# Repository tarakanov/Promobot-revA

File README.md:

Promobot
=============

Main board for Promobot, robotic platform. Still in development.

Schematic and layout done in Eagle.
Board has four VNH5019A-E H-bridge drivers for high current DC brushed motors, 50W 2ch audio amplifier (TPA116D2), two DC/DC step-up converters (TPS43061, up to 40V, 20A), one DC/DC step-down converter (TPS563200, 5V, 3A) and MCU for control (atmega32u4, Arduino Leonardo compatible).

It is initial design, so the board is big and bulky (15x15 cm). The board is manufactured and tested, but the current and power limits was not reached. There is a lot things to cut. Feel free to ask questions and make improvements.

Designed by Semyon Tarakanov. Creative Commons Attribution, Share-Alike license.

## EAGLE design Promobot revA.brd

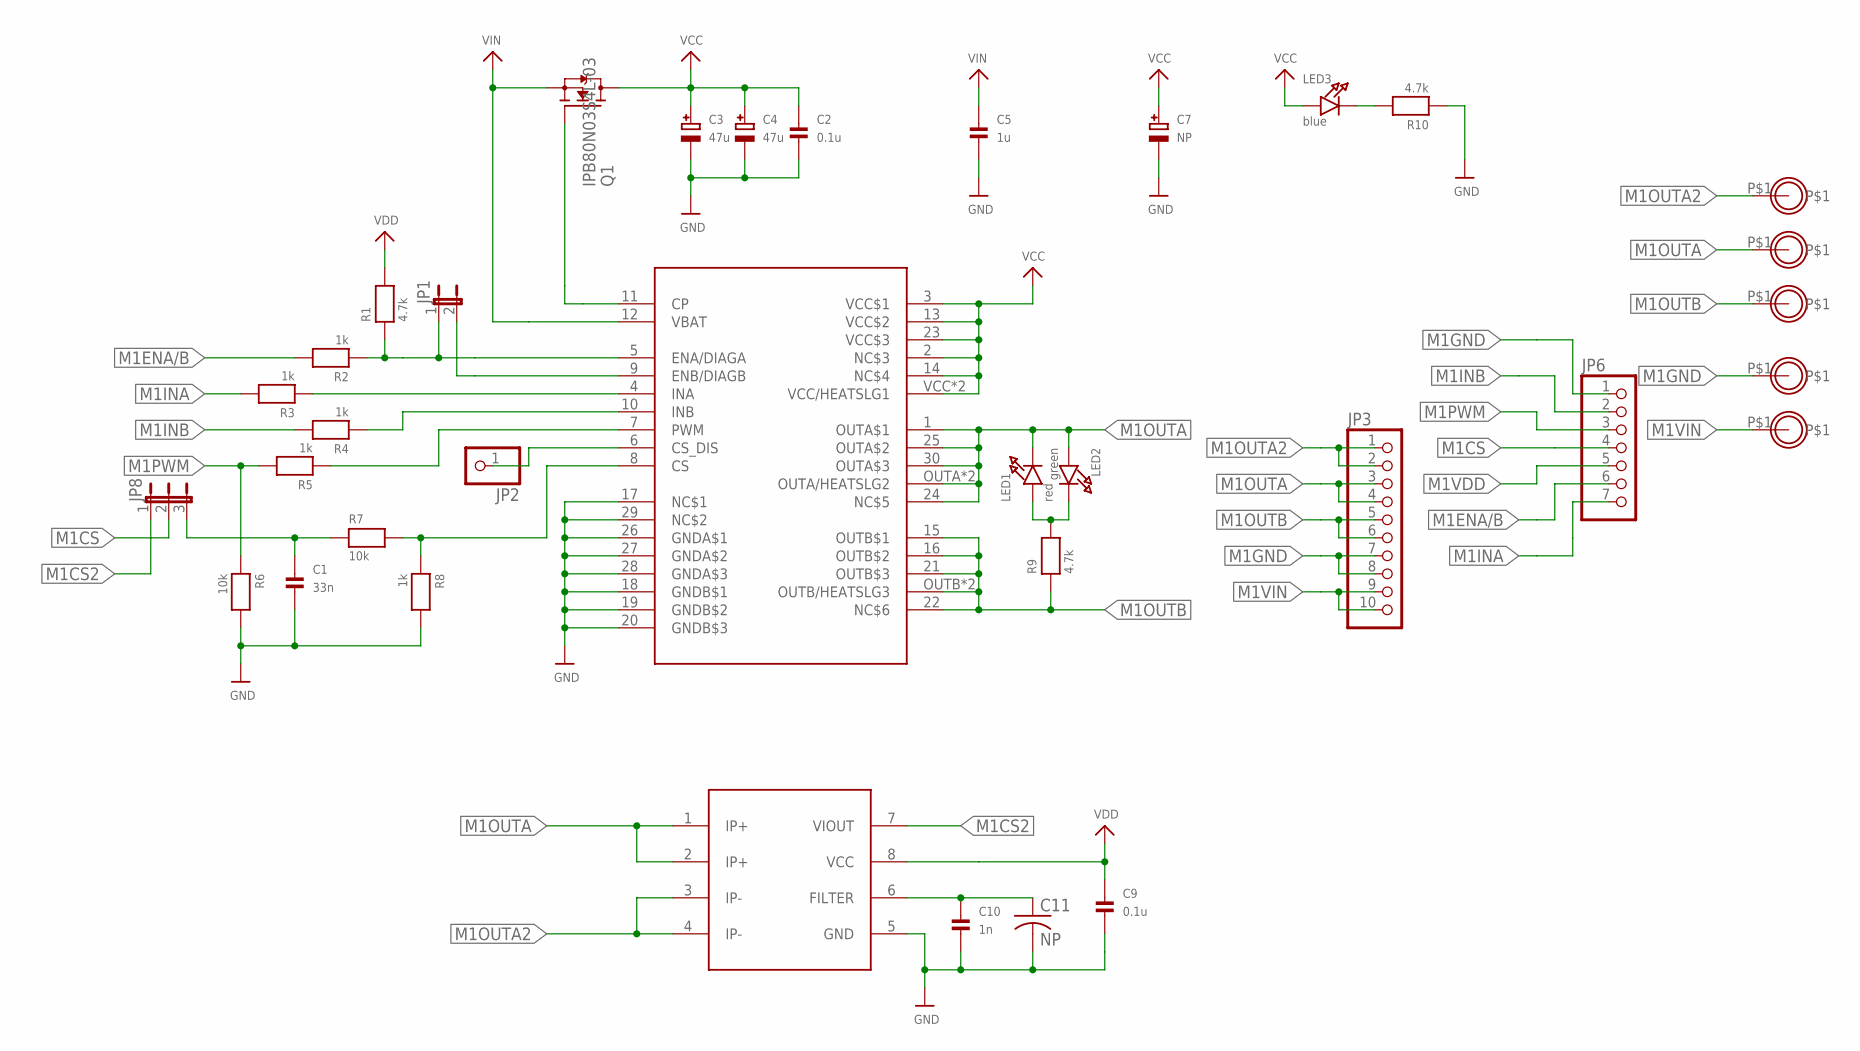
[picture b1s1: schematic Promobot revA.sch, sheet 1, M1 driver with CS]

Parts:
C1: 33n; _0603
C2, C9: 0.1u; _0603
C3, C4: 47u; PANASONIC_C
C5: 1u; _0805
C7: NP; CELEC_3.5MM_10MM
C10: 1n; _0603
C11: NP; C025-024X044
JP1: JUMPER2
JP2: HEADER-1X1ROUND; 1X01_ROUND
JP3: HEADER-1X10ROUND; 1X10_ROUND
JP6: HEADER-1X7ROUND; 1X07_ROUND
JP8: JUMPER3
LED1: red; CHIPLED_0603
LED2: green; CHIPLED_0603
LED3: blue; CHIPLED_0603
M1OUTA, M1OUTA1, M1OUTA3, M1OUTA4, M1OUTB: MOUNTINGHOLE2.5_THICK; MOUNTINGHOLE_2.5_PLATED_THICK
Q1: IPB80N03S4L-03; TO263
R1, R9, R10: 4.7k; 0603
R2, R3, R4, R5, R8: 1k; 0603
R6, R7: 10k; 0603
U1: VNH5019A-E; MULTIPOWERSO-30
U2: ACS714; SOIC8_208MIL

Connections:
M1CS: JP6.4, JP8.2
M1CS1: C1.1, JP8.3, R7.1
M1CS2: JP8.1, U2.7 (VIOUT)
M1ENA/B: JP6.6, R2.2
M1GND: C1.2, C2.2, C3.-, C4.-, C5.2, C7.-, C9.2, C10.2, C11.2, JP3.7, JP3.8, JP6.1, M1OUTA3.P$1, R6.2, R8.2, R10.1, U1.17 (NC$1), U1.18 (GNDB$1), U1.19 (GNDB$2), U1.20 (GNDB$3), U1.26 (GNDA$1), U1.27 (GNDA$2), U1.28 (GNDA$3), U1.29 (NC$2), U2.5 (GND); also elsewhere on the board
M1INA: JP6.7, R3.2
M1INB: JP6.2, R4.2
M1OUTA: JP3.3, JP3.4, LED1.C, LED2.A, M1OUTA1.P$1, U1.1 (OUTA$1), U1.24 (NC$5), U1.25 (OUTA$2), U1.30 (OUTA$3), U1.OUTA (OUTA/HEATSLG2), U1.OUTA@1 (OUTA/HEATSLG2), U2.1 (IP+), U2.2 (IP+)
M1OUTA2: JP3.1, JP3.2, M1OUTA.P$1, U2.3 (IP-), U2.4 (IP-)
M1OUTB: JP3.5, JP3.6, M1OUTB.P$1, R9.1, U1.15 (OUTB$1), U1.16 (OUTB$2), U1.21 (OUTB$3), U1.22 (NC$6), U1.OUTB (OUTB/HEATSLG3), U1.OUTB@1 (OUTB/HEATSLG3)
M1PWM: JP6.3, R5.2, R6.1
M1VCC: C2.1, C3.+, C4.+, C7.+, LED3.A, Q1.3 (D), U1.2 (NC$3), U1.3 (VCC$1), U1.13 (VCC$2), U1.14 (NC$4), U1.23 (VCC$3), U1.VCC (VCC/HEATSLG1), U1.VCC@1 (VCC/HEATSLG1); also elsewhere on the board
M1VDD: C9.1, JP6.5, R1.2, U2.8 (VCC)
M1VIN: C5.1, JP3.9, JP3.10, M1OUTA4.P$1, Q1.2 (S), U1.12 (VBAT)
unnamed: Q1.1 (G), U1.11 (CP)
unnamed: JP1.2, U1.9 (ENB/DIAGB)
unnamed: R5.1, U1.7 (PWM)
unnamed: JP1.1, R1.1, R2.1, U1.5 (ENA/DIAGA)
unnamed: R7.2, R8.1, U1.8 (CS)
unnamed: R3.1, U1.4 (INA)
unnamed: R4.1, U1.10 (INB)
unnamed: JP2.1, U1.6 (CS_DIS)
unnamed: LED3.C, R10.2
unnamed: C10.1, C11.1, U2.6 (FILTER)
unnamed: LED1.A, LED2.C, R9.2

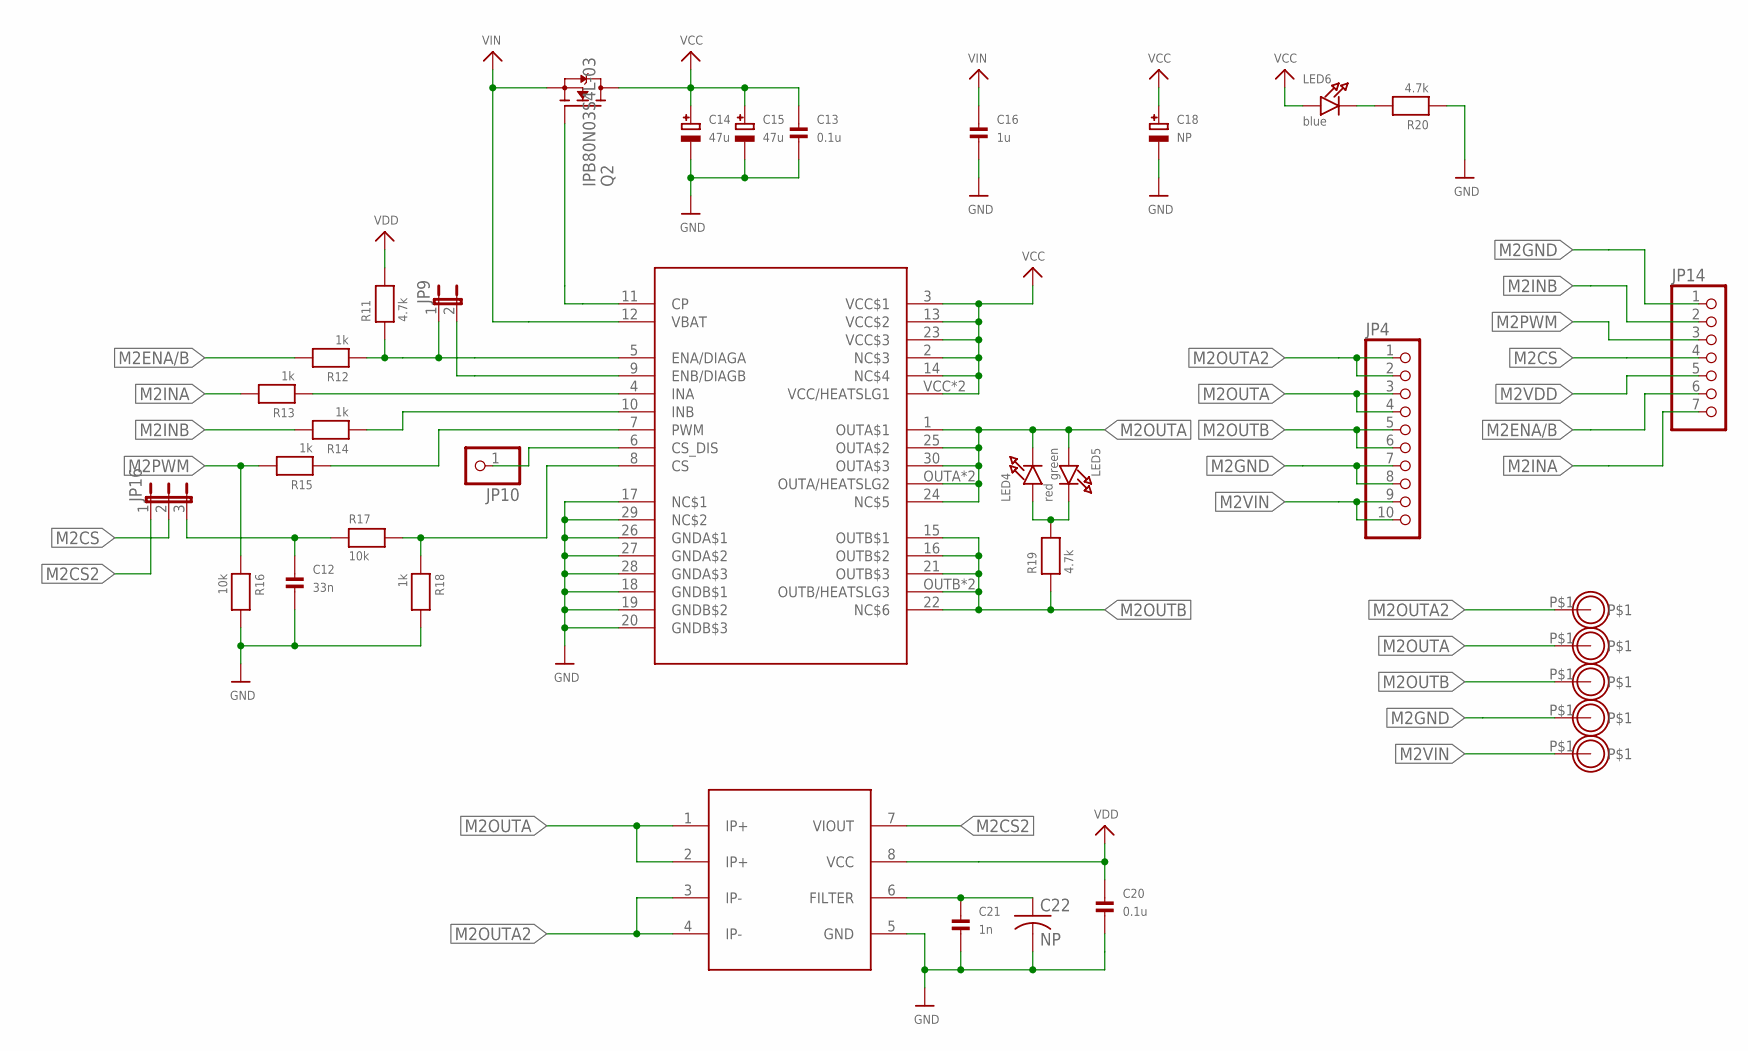
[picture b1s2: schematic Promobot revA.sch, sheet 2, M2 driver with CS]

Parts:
C12: 33n; _0603
C13, C20: 0.1u; _0603
C14, C15: 47u; PANASONIC_C
C16: 1u; _0805
C18: NP; CELEC_3.5MM_10MM
C21: 1n; _0603
C22: NP; C025-024X044
JP4: HEADER-1X10ROUND; 1X10_ROUND
JP9: JUMPER2
JP10: HEADER-1X1ROUND; 1X01_ROUND
JP14: HEADER-1X7ROUND; 1X07_ROUND
JP16: JUMPER3
LED4: red; CHIPLED_0603
LED5: green; CHIPLED_0603
LED6: blue; CHIPLED_0603
M1OUTA2, M1OUTA5, M1OUTA6, M1OUTA7, M1OUTB1: MOUNTINGHOLE2.5_THICK; MOUNTINGHOLE_2.5_PLATED_THICK
Q2: IPB80N03S4L-03; TO263
R11, R19, R20: 4.7k; 0603
R12, R13, R14, R15, R18: 1k; 0603
R16, R17: 10k; 0603
U3: VNH5019A-E; MULTIPOWERSO-30
U4: ACS714; SOIC8_208MIL

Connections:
M2CS: JP14.4, JP16.2
M2CS2: JP16.1, U4.7 (VIOUT)
M2ENA/B: JP14.6, R12.2
M2GND: C12.2, C13.2, C14.-, C15.-, C16.2, C18.-, C20.2, C21.2, C22.2, JP4.7, JP4.8, JP14.1, M1OUTA6.P$1, R16.2, R18.2, R20.1, U3.17 (NC$1), U3.18 (GNDB$1), U3.19 (GNDB$2), U3.20 (GNDB$3), U3.26 (GNDA$1), U3.27 (GNDA$2), U3.28 (GNDA$3), U3.29 (NC$2), U4.5 (GND); also elsewhere on the board
M2INA: JP14.7, R13.2
M2INB: JP14.2, R14.2
M2OUTA: JP4.3, JP4.4, LED4.C, LED5.A, M1OUTA5.P$1, U3.1 (OUTA$1), U3.24 (NC$5), U3.25 (OUTA$2), U3.30 (OUTA$3), U3.OUTA (OUTA/HEATSLG2), U3.OUTA@1 (OUTA/HEATSLG2), U4.1 (IP+), U4.2 (IP+)
M2OUTA2: JP4.1, JP4.2, M1OUTA2.P$1, U4.3 (IP-), U4.4 (IP-)
M2OUTB: JP4.5, JP4.6, M1OUTB1.P$1, R19.1, U3.15 (OUTB$1), U3.16 (OUTB$2), U3.21 (OUTB$3), U3.22 (NC$6), U3.OUTB (OUTB/HEATSLG3), U3.OUTB@1 (OUTB/HEATSLG3)
M2PWM: JP14.3, R15.2, R16.1
M2VCC: C13.1, C14.+, C15.+, C18.+, LED6.A, Q2.3 (D), U3.2 (NC$3), U3.3 (VCC$1), U3.13 (VCC$2), U3.14 (NC$4), U3.23 (VCC$3), U3.VCC (VCC/HEATSLG1), U3.VCC@1 (VCC/HEATSLG1); also elsewhere on the board
M2VDD: C20.1, JP14.5, R11.2, U4.8 (VCC)
M2VIN: C16.1, JP4.9, JP4.10, M1OUTA7.P$1, Q2.2 (S), U3.12 (VBAT)
unnamed: Q2.1 (G), U3.11 (CP)
unnamed: JP9.1, R11.1, R12.1, U3.5 (ENA/DIAGA)
unnamed: JP9.2, U3.9 (ENB/DIAGB)
unnamed: R13.1, U3.4 (INA)
unnamed: R14.1, U3.10 (INB)
unnamed: R15.1, U3.7 (PWM)
unnamed: R17.2, R18.1, U3.8 (CS)
unnamed: JP10.1, U3.6 (CS_DIS)
unnamed: LED4.A, LED5.C, R19.2
unnamed: LED6.C, R20.2
unnamed: C21.1, C22.1, U4.6 (FILTER)
unnamed: C12.1, JP16.3, R17.1

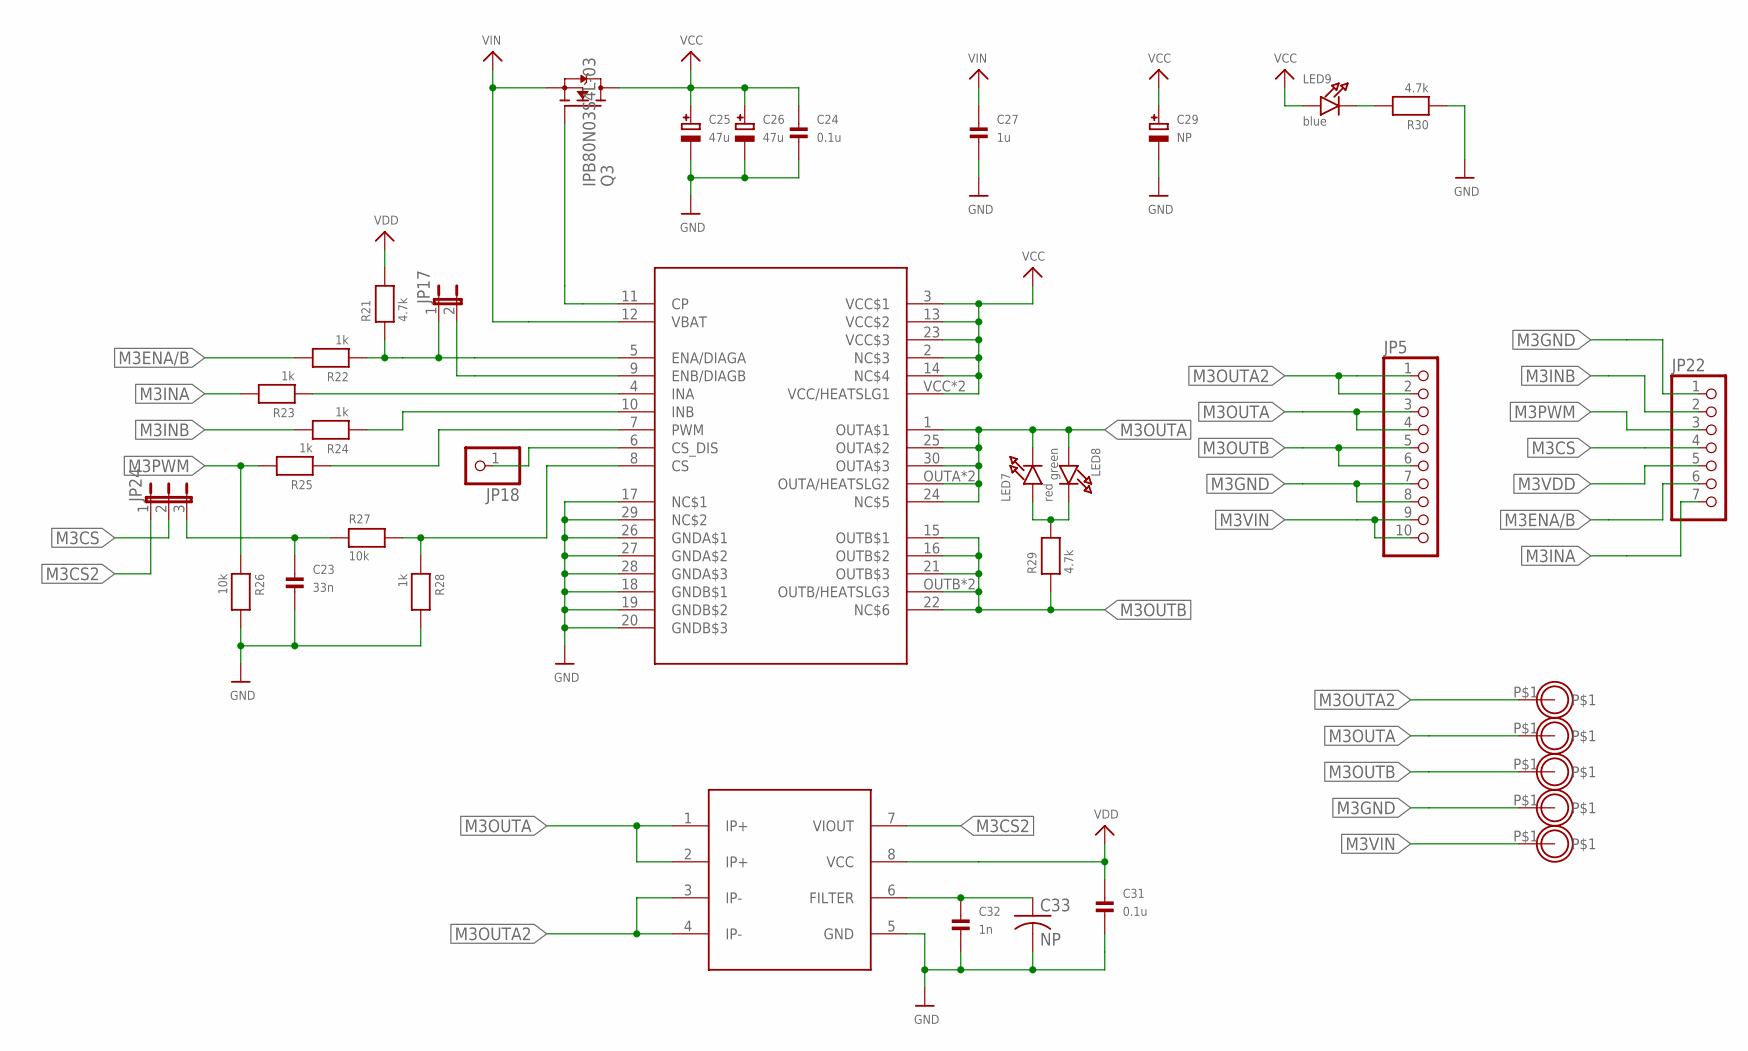
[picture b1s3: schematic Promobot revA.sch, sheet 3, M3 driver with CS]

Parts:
C23: 33n; _0603
C24, C31: 0.1u; _0603
C25, C26: 47u; PANASONIC_C
C27: 1u; _0805
C29: NP; CELEC_3.5MM_10MM
C32: 1n; _0603
C33: NP; C025-024X044
JP5: HEADER-1X10ROUND; 1X10_ROUND
JP17: JUMPER2
JP18: HEADER-1X1ROUND; 1X01_ROUND
JP22: HEADER-1X7ROUND; 1X07_ROUND
JP24: JUMPER3
LED7: red; CHIPLED_0603
LED8: green; CHIPLED_0603
LED9: blue; CHIPLED_0603
M1OUTA8, M1OUTA9, M1OUTA10, M1OUTA11, M1OUTB2: MOUNTINGHOLE2.5_THICK; MOUNTINGHOLE_2.5_PLATED_THICK
Q3: IPB80N03S4L-03; TO263
R21, R29, R30: 4.7k; 0603
R22, R23, R24, R25, R28: 1k; 0603
R26, R27: 10k; 0603
U5: VNH5019A-E; MULTIPOWERSO-30
U6: ACS714; SOIC8_208MIL

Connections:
M3CS: JP22.4, JP24.2
M3CS2: JP24.1, U6.7 (VIOUT)
M3ENA/B: JP22.6, R22.2
M3GND: C23.2, C24.2, C25.-, C26.-, C27.2, C29.-, C31.2, C32.2, C33.2, JP5.7, JP5.8, JP22.1, M1OUTA10.P$1, R26.2, R28.2, R30.1, U5.17 (NC$1), U5.18 (GNDB$1), U5.19 (GNDB$2), U5.20 (GNDB$3), U5.26 (GNDA$1), U5.27 (GNDA$2), U5.28 (GNDA$3), U5.29 (NC$2), U6.5 (GND); also elsewhere on the board
M3INA: JP22.7, R23.2
M3INB: JP22.2, R24.2
M3OUTA: JP5.3, JP5.4, LED7.C, LED8.A, M1OUTA9.P$1, U5.1 (OUTA$1), U5.24 (NC$5), U5.25 (OUTA$2), U5.30 (OUTA$3), U5.OUTA (OUTA/HEATSLG2), U5.OUTA@1 (OUTA/HEATSLG2), U6.1 (IP+), U6.2 (IP+)
M3OUTA2: JP5.1, JP5.2, M1OUTA8.P$1, U6.3 (IP-), U6.4 (IP-)
M3OUTB: JP5.5, JP5.6, M1OUTB2.P$1, R29.1, U5.15 (OUTB$1), U5.16 (OUTB$2), U5.21 (OUTB$3), U5.22 (NC$6), U5.OUTB (OUTB/HEATSLG3), U5.OUTB@1 (OUTB/HEATSLG3)
M3PWM: JP22.3, R25.2, R26.1
M3VCC: C24.1, C25.+, C26.+, C29.+, LED9.A, Q3.3 (D), U5.2 (NC$3), U5.3 (VCC$1), U5.13 (VCC$2), U5.14 (NC$4), U5.23 (VCC$3), U5.VCC (VCC/HEATSLG1), U5.VCC@1 (VCC/HEATSLG1); also elsewhere on the board
M3VDD: C31.1, JP22.5, R21.2, U6.8 (VCC)
M3VIN: C27.1, JP5.9, JP5.10, M1OUTA11.P$1, Q3.2 (S), U5.12 (VBAT)
unnamed: Q3.1 (G), U5.11 (CP)
unnamed: JP17.1, R21.1, R22.1, U5.5 (ENA/DIAGA)
unnamed: JP17.2, U5.9 (ENB/DIAGB)
unnamed: R23.1, U5.4 (INA)
unnamed: R24.1, U5.10 (INB)
unnamed: R25.1, U5.7 (PWM)
unnamed: R27.2, R28.1, U5.8 (CS)
unnamed: JP18.1, U5.6 (CS_DIS)
unnamed: LED7.A, LED8.C, R29.2
unnamed: LED9.C, R30.2
unnamed: C32.1, C33.1, U6.6 (FILTER)
unnamed: C23.1, JP24.3, R27.1

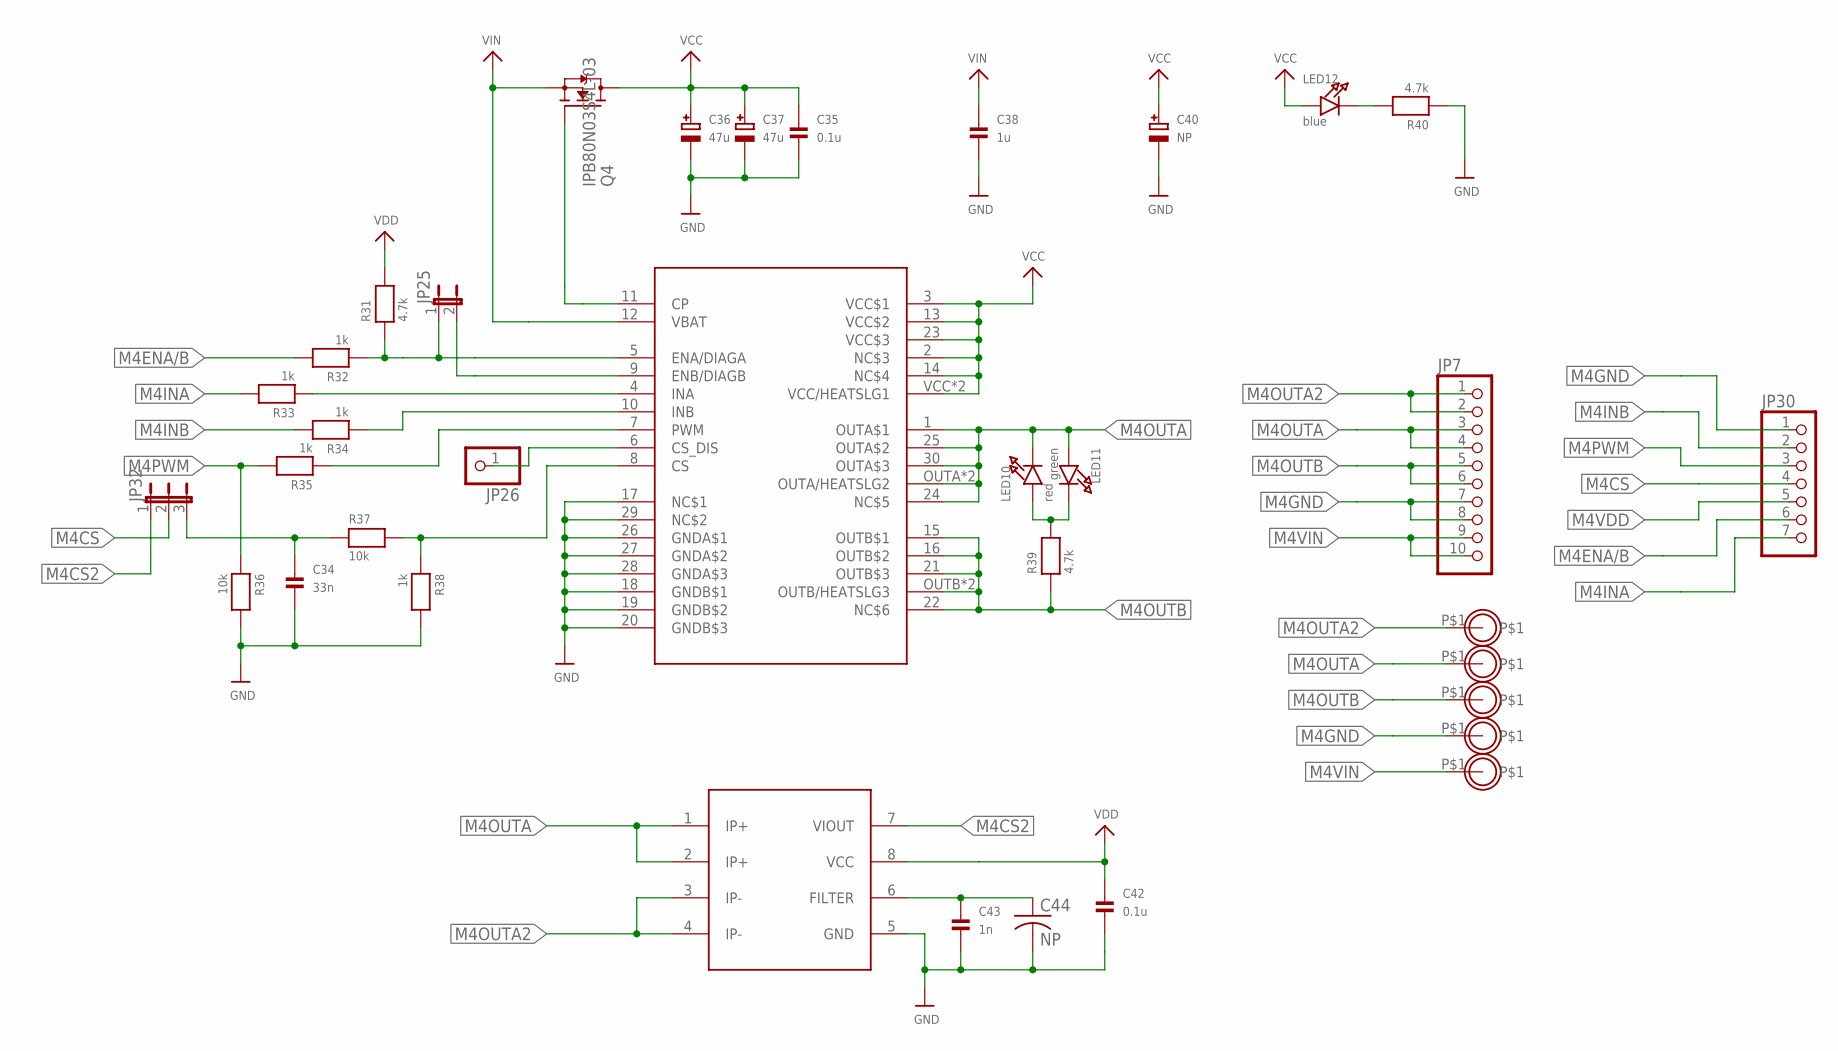
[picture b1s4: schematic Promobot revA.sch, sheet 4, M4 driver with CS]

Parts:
C34: 33n; _0603
C35, C42: 0.1u; _0603
C36, C37: 47u; PANASONIC_C
C38: 1u; _0805
C40: NP; CELEC_3.5MM_10MM
C43: 1n; _0603
C44: NP; C025-024X044
JP7: HEADER-1X10ROUND; 1X10_ROUND
JP25: JUMPER2
JP26: HEADER-1X1ROUND; 1X01_ROUND
JP30: HEADER-1X7ROUND; 1X07_ROUND
JP32: JUMPER3
LED10: red; CHIPLED_0603
LED11: green; CHIPLED_0603
LED12: blue; CHIPLED_0603
M1OUTA12, M1OUTA13, M1OUTA14, M1OUTA15, M1OUTB3: MOUNTINGHOLE2.5_THICK; MOUNTINGHOLE_2.5_PLATED_THICK
Q4: IPB80N03S4L-03; TO263
R31, R39, R40: 4.7k; 0603
R32, R33, R34, R35, R38: 1k; 0603
R36, R37: 10k; 0603
U7: VNH5019A-E; MULTIPOWERSO-30
U8: ACS714; SOIC8_208MIL

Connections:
M4CS: JP30.4, JP32.2
M4CS2: JP32.1, U8.7 (VIOUT)
M4ENA/B: JP30.6, R32.2
M4GND: C34.2, C35.2, C36.-, C37.-, C38.2, C40.-, C42.2, C43.2, C44.2, JP7.7, JP7.8, JP30.1, M1OUTA14.P$1, R36.2, R38.2, R40.1, U7.17 (NC$1), U7.18 (GNDB$1), U7.19 (GNDB$2), U7.20 (GNDB$3), U7.26 (GNDA$1), U7.27 (GNDA$2), U7.28 (GNDA$3), U7.29 (NC$2), U8.5 (GND); also elsewhere on the board
M4INA: JP30.7, R33.2
M4INB: JP30.2, R34.2
M4OUTA: JP7.3, JP7.4, LED10.C, LED11.A, M1OUTA13.P$1, U7.1 (OUTA$1), U7.24 (NC$5), U7.25 (OUTA$2), U7.30 (OUTA$3), U7.OUTA (OUTA/HEATSLG2), U7.OUTA@1 (OUTA/HEATSLG2), U8.1 (IP+), U8.2 (IP+)
M4OUTA2: JP7.1, JP7.2, M1OUTA12.P$1, U8.3 (IP-), U8.4 (IP-)
M4OUTB: JP7.5, JP7.6, M1OUTB3.P$1, R39.1, U7.15 (OUTB$1), U7.16 (OUTB$2), U7.21 (OUTB$3), U7.22 (NC$6), U7.OUTB (OUTB/HEATSLG3), U7.OUTB@1 (OUTB/HEATSLG3)
M4PWM: JP30.3, R35.2, R36.1
M4VCC: C35.1, C36.+, C37.+, C40.+, LED12.A, Q4.3 (D), U7.2 (NC$3), U7.3 (VCC$1), U7.13 (VCC$2), U7.14 (NC$4), U7.23 (VCC$3), U7.VCC (VCC/HEATSLG1), U7.VCC@1 (VCC/HEATSLG1); also elsewhere on the board
M4VDD: C42.1, JP30.5, R31.2, U8.8 (VCC)
M4VIN: C38.1, JP7.9, JP7.10, M1OUTA15.P$1, Q4.2 (S), U7.12 (VBAT)
unnamed: Q4.1 (G), U7.11 (CP)
unnamed: JP25.1, R31.1, R32.1, U7.5 (ENA/DIAGA)
unnamed: JP25.2, U7.9 (ENB/DIAGB)
unnamed: R33.1, U7.4 (INA)
unnamed: R34.1, U7.10 (INB)
unnamed: R35.1, U7.7 (PWM)
unnamed: R37.2, R38.1, U7.8 (CS)
unnamed: JP26.1, U7.6 (CS_DIS)
unnamed: LED10.A, LED11.C, R39.2
unnamed: LED12.C, R40.2
unnamed: C43.1, C44.1, U8.6 (FILTER)
unnamed: C34.1, JP32.3, R37.1

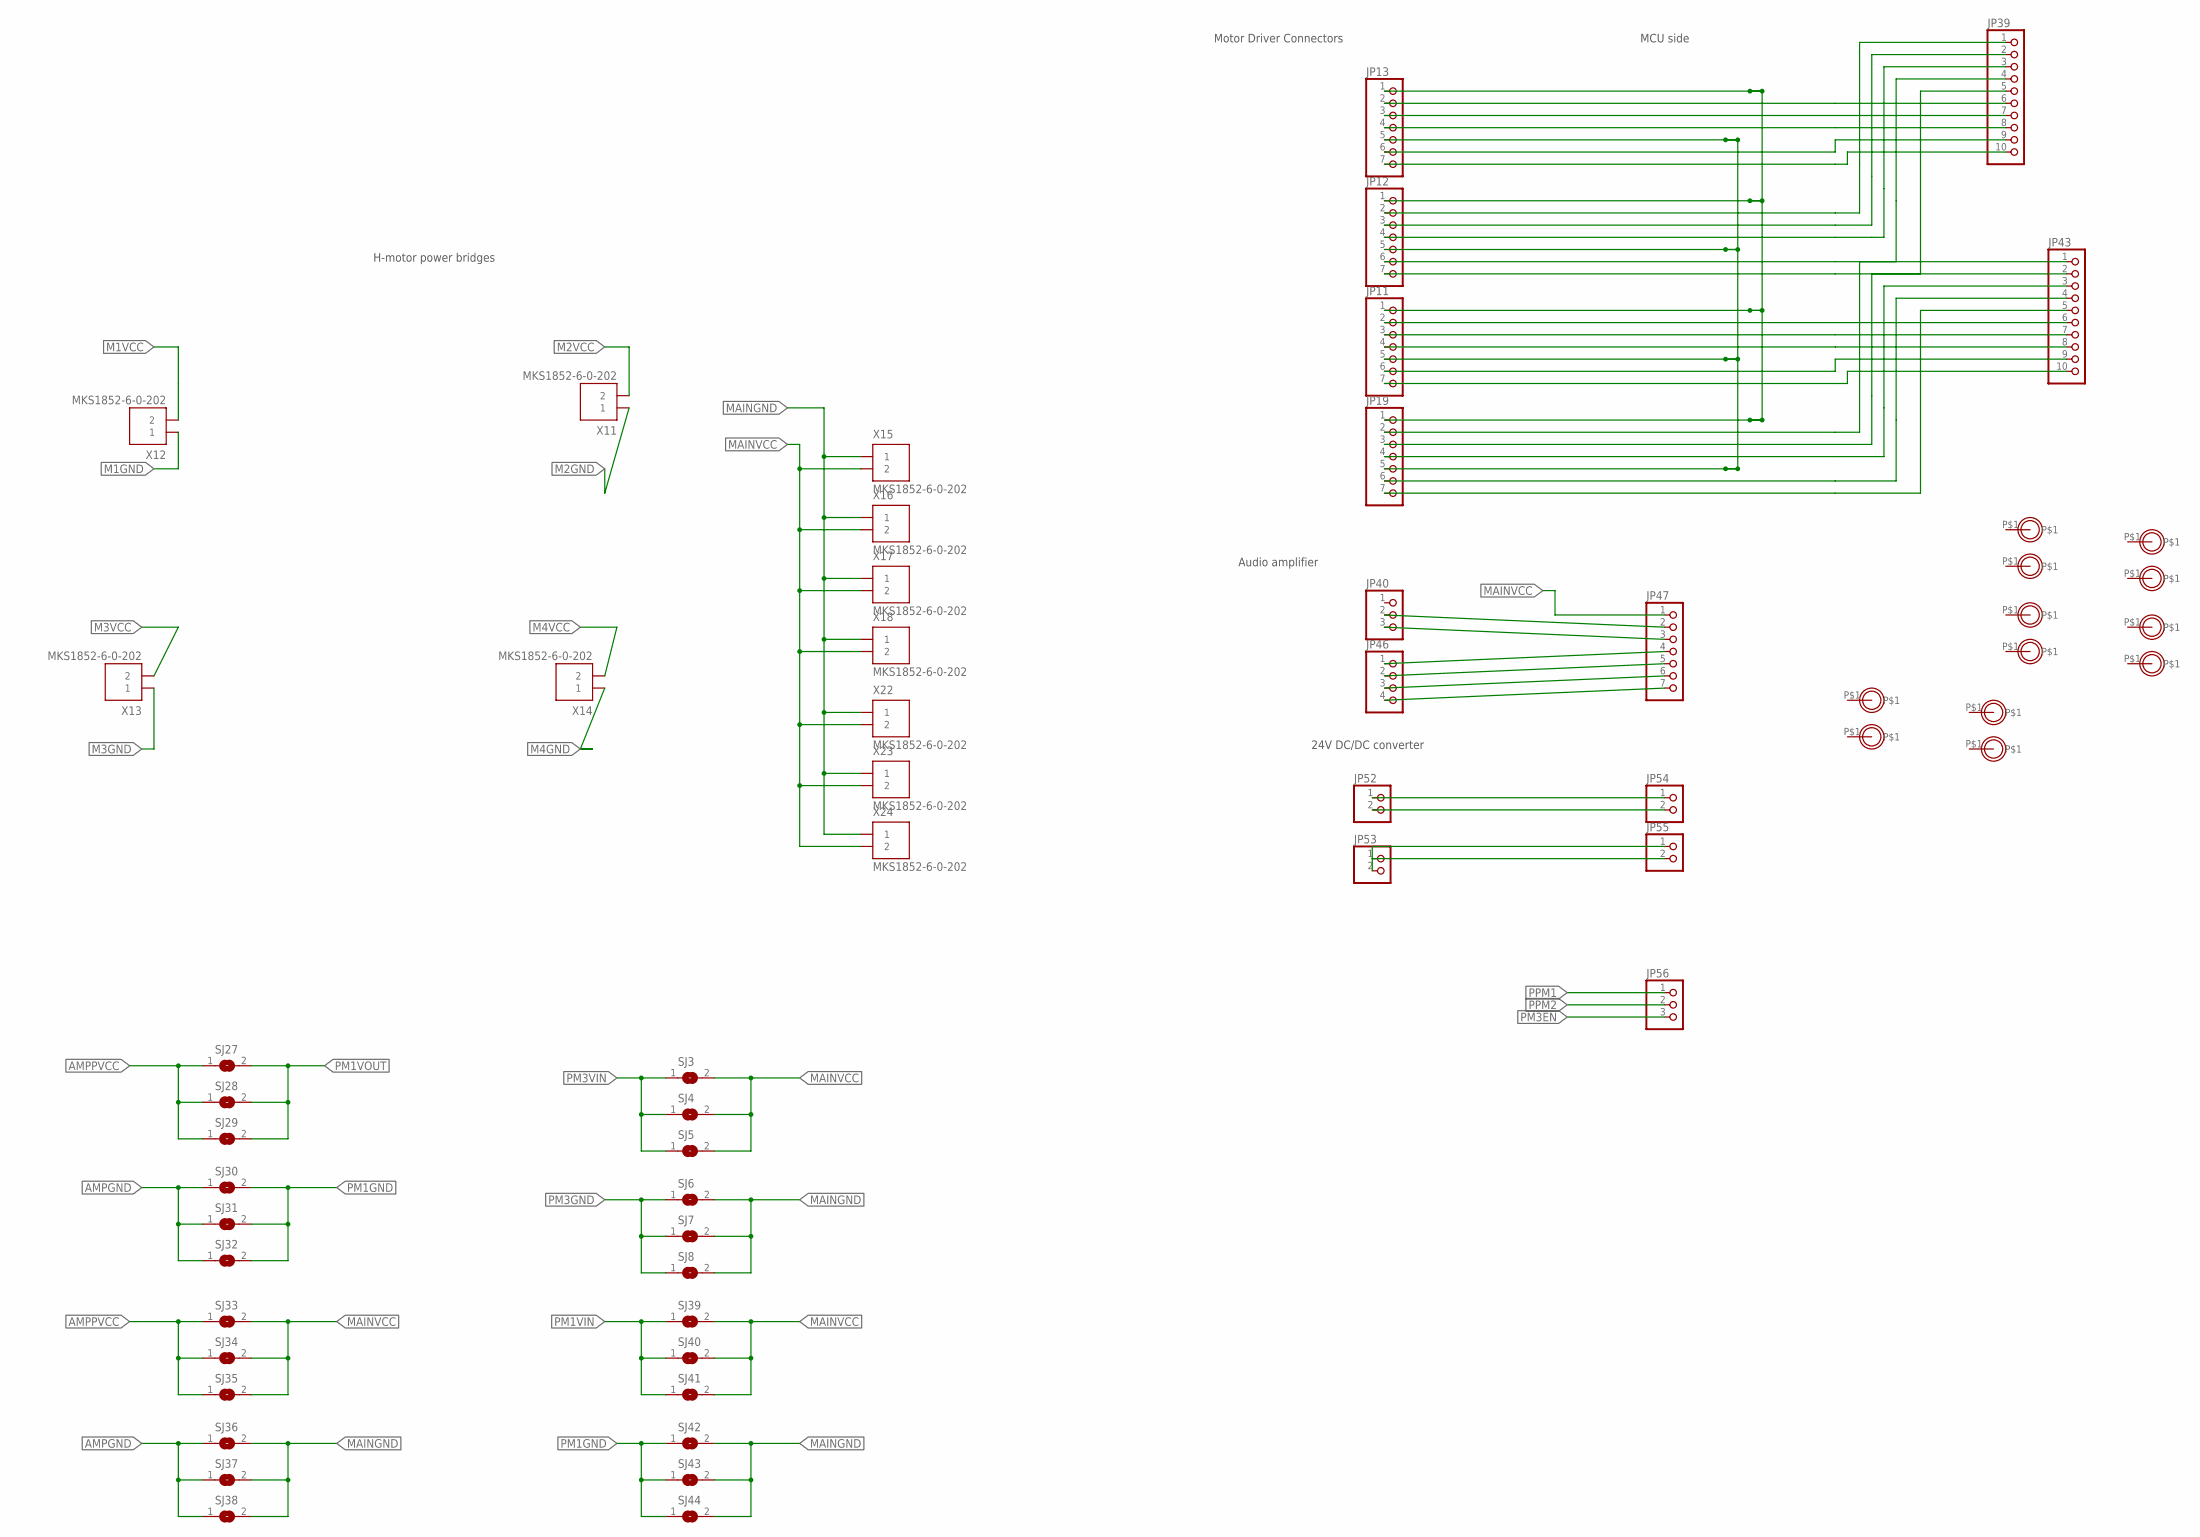
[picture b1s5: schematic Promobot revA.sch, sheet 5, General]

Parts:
JP11, JP12, JP13, JP19, JP47: HEADER-1X7ROUND; 1X07_ROUND
JP39, JP43: HEADER-1X1070MIL; 1X10_ROUND70
JP40: HEADER-1X376MIL; 1X03_ROUND_76
JP46: HEADER-1X476MIL; 1X04_ROUND_76
JP52, JP53, JP54, JP55: HEADER-1X2ROUND; 1X02_ROUND
JP56: HEADER-1X3ROUND; 1X03_ROUND
M1OUTA16, M1OUTA17, M1OUTA18, M1OUTA19, M1OUTA20, M1OUTA21, M1OUTA22, M1OUTA23, M1OUTA24, M1OUTA25, M1OUTB4, M1OUTB5: MOUNTINGHOLE2.5_THICK; MOUNTINGHOLE_2.5_PLATED_THICK
SJ3, SJ4, SJ5, SJ6, SJ7, SJ8, SJ27, SJ28, SJ29, SJ30, SJ31, SJ32, SJ33, SJ34, SJ35, SJ36, SJ37, SJ38, SJ39, SJ40, SJ41, SJ42, SJ43, SJ44: SOLDERJUMPER; SOLDERJUMPER_ARROW_NOPASTE
X11, X12, X13, X14, X15, X16, X17, X18, X22, X23, X24: MKS1852-6-0-202

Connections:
AMPGND: SJ30.1, SJ31.1, SJ32.1, SJ36.1, SJ37.1, SJ38.1; also elsewhere on the board
AMPPVCC: SJ27.1, SJ28.1, SJ29.1, SJ33.1, SJ34.1, SJ35.1; also elsewhere on the board
M1GND: X12.1; also elsewhere on the board
M1VCC: X12.2; also elsewhere on the board
M2GND: X11.1; also elsewhere on the board
M2VCC: X11.2; also elsewhere on the board
M3GND: X13.1; also elsewhere on the board
M3VCC: X13.2; also elsewhere on the board
M4GND: X14.1; also elsewhere on the board
M4VCC: X14.2; also elsewhere on the board
MAINGND: JP11.1, JP12.1, JP13.1, JP19.1, SJ6.2, SJ7.2, SJ8.2, SJ36.2, SJ37.2, SJ38.2, SJ42.2, SJ43.2, SJ44.2, X15.1, X16.1, X17.1, X18.1, X22.1, X23.1, X24.1
MAINVCC: JP11.5, JP12.5, JP13.5, JP19.5, JP47.1, SJ3.2, SJ4.2, SJ5.2, SJ33.2, SJ34.2, SJ35.2, SJ39.2, SJ40.2, SJ41.2, X15.2, X16.2, X17.2, X18.2, X22.2, X23.2, X24.2
unnamed: JP52.1, JP54.1
unnamed: JP52.2, JP54.2
unnamed: JP13.2, JP39.6
unnamed: JP13.3, JP39.7
unnamed: JP13.4, JP39.8
unnamed: JP40.2, JP47.2
unnamed: JP13.6, JP39.9
unnamed: JP13.7, JP39.10
unnamed: JP12.2, JP39.1
unnamed: JP12.3, JP39.2
unnamed: JP12.4, JP39.3
unnamed: JP12.6, JP39.4
unnamed: JP12.7, JP39.5
unnamed: JP40.3, JP47.3
unnamed: JP11.2, JP43.6
unnamed: JP11.3, JP43.7
unnamed: JP11.4, JP43.8
unnamed: JP46.1, JP47.4
unnamed: JP11.6, JP43.9
unnamed: JP11.7, JP43.10
unnamed: JP46.2, JP47.5
unnamed: JP19.2, JP43.1
unnamed: JP19.3, JP43.2
unnamed: JP19.4, JP43.3
unnamed: JP46.3, JP47.6
unnamed: JP19.6, JP43.4
unnamed: JP19.7, JP43.5
unnamed: JP46.4, JP47.7
unnamed: JP53.1, JP55.1
unnamed: JP53.2, JP55.2
PM1GND: SJ30.2, SJ31.2, SJ32.2, SJ42.1, SJ43.1, SJ44.1; also elsewhere on the board
PM1VIN: SJ39.1, SJ40.1, SJ41.1; also elsewhere on the board
PM1VOUT: SJ27.2, SJ28.2, SJ29.2; also elsewhere on the board
PM3EN: JP56.3; also elsewhere on the board
PM3GND: SJ6.1, SJ7.1, SJ8.1; also elsewhere on the board
PM3VIN: SJ3.1, SJ4.1, SJ5.1; also elsewhere on the board
PPM1: JP56.1; also elsewhere on the board
PPM2: JP56.2; also elsewhere on the board

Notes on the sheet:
Motor Driver Connectors
MCU side
Audio amplifier
24V DC/DC converter
H-motor power bridges

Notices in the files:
parts and their libraries:
microbuilder: This work is placed in the public domain, and may be freely used for commercial and non-commercial work with the following conditions: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
